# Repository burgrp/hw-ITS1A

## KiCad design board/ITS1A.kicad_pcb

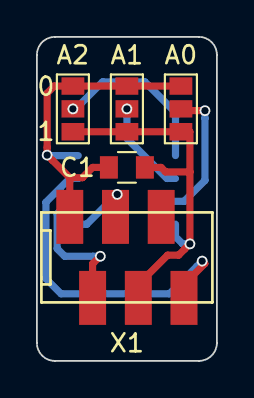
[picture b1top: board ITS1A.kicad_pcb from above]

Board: 2 copper layers, 10.0 x 18.0 mm, 6 parts (1 on the bottom side), 8 nets.

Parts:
A0, A1, A2: GS3
C1: 100n; C_0805
U1: LM75A; SOIC-8_3.9x4.9mm_Pitch1.27mm
X1: I2C-6P; Micro-Match-FOB-6

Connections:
/ALERT: U1.3, X1.6
/SCL: U1.2, X1.2
/SDA: U1.1, X1.3
GND: A0.1, A1.1, A2.1, C1.2, U1.4, X1.1
unnamed: A0.2, U1.7
unnamed: A1.2, U1.6
unnamed: A2.2, U1.5
VCC: A0.3, A1.3, A2.3, C1.1, U1.8, X1.4
